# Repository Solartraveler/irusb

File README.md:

# IRUSB
This project is is a small board for sending infrared controller codes from a PC.
Receiving IR codes is possible too, but was not the main objective of this project.

## Host program

A host program for communicating is provided.
Written in python, it is platform independent - Linux and Windows were tested.

It all goes down to call the program like

./irusb-control.py 2 0xff00 0

Where the first parameter is the protocol, the second the address and the third the command.

You can add a TSOP31236 and call the host program without a parameter. Then press the key, you want to send later, on your existing infrared remote. The program then will print out the protocol, address and command discovered.

When installing the debian package, the same program can be called by the name irusb-control.

## Compiling and uploading

There is no additional programming hardware needed.

With apt install the packages gcc-arm-none-eabi, make, dfu-util and python3-usb.

Next, call make

Then close J4 and call ./dfu-upload.sh

Later, leave J4 open to directly start the flashed program.

## Debugging

You can add a serial port with 3.3V level to J3 and see some debug messages when using 19200baud.

Tested with a [NUCLEO-F411RE](https://www.st.com/en/evaluation-tools/nucleo-f411re.html), the software can be debugged. Open jumpers CN2 on the nucleo board and connect pins 2,3,4,5 of CN4 to the pins 2,3,4,5 of J2 on the IRUSB pcb.

## TODO

Create and publish a kicad symbol for a MCP1754-3302E_SOT23

## Libraries used and licenses

The software uses several open source libraries with different licenses.

The HAL library from ST is published under the BSD 3-Clause license.

Some CMSIS header files are published under the Apache 2.0 license.

The [IRMP](https://www.mikrocontroller.net/articles/IRMP_-_english) project is published under GPL 2.0 or later.

[Libusb_stm32](https://github.com/dmitrystu/libusb_stm32) is published under the Apache 2.0 license.

Since GPL 2.0 and Apache 2.0 are considered [incompatible](https://www.apache.org/licenses/GPL-compatibility.html) by the Free Software Foundation, but GPL 3.0 is considered compatible, GPL 3.0 is the only possible license for the firmware on the microcontroller side.

The PCB is under creative common license. [CC-BY-SA 3.0 DE](https://creativecommons.org/licenses/by-sa/3.0/de/deed.en)

## Windows users

Windows makes using USB devices a little bit more difficult. These steps are tested with Windows 10 64bit version 1903.

Install [python 3.9 for windows](https://www.python.org/downloads/windows/) and allow adding python to PATH.

Start cmd

Install pyusb with pip3 install pyusb

Now calling irusb-control.py will result in the error message "No backed available."

You will need a windows driver for IRUSB. [libusbK-inf-wizard.exe](https://sourceforge.net/projects/libusb-win32/files/libusb-win32-releases/libusbK-inf-wizard.exe) can generate one. I tried kernel driver package libusb0 v1.2.6.0. Select IRUSB (VID = 0x7700), then in the generated DriverPackages directory call InstallDriver.exe.

Now calling irusb-control.py should work.

## Alternate usage

The PCB can be used as simple testing board for other projects too. The project [stm32-verprog](https://github.com/dword1511/stm32-vserprog/) had already support for the same STM32 chip as used for IRUSB. So using a spare PCB as SPI flash chip programmer was easy.

Note: The socket shown on the picture is only 150mil in width, but flash chips typically require 200mil wide ones. So the flash chip is inserted upside down and the wires are mirrored accordingly.

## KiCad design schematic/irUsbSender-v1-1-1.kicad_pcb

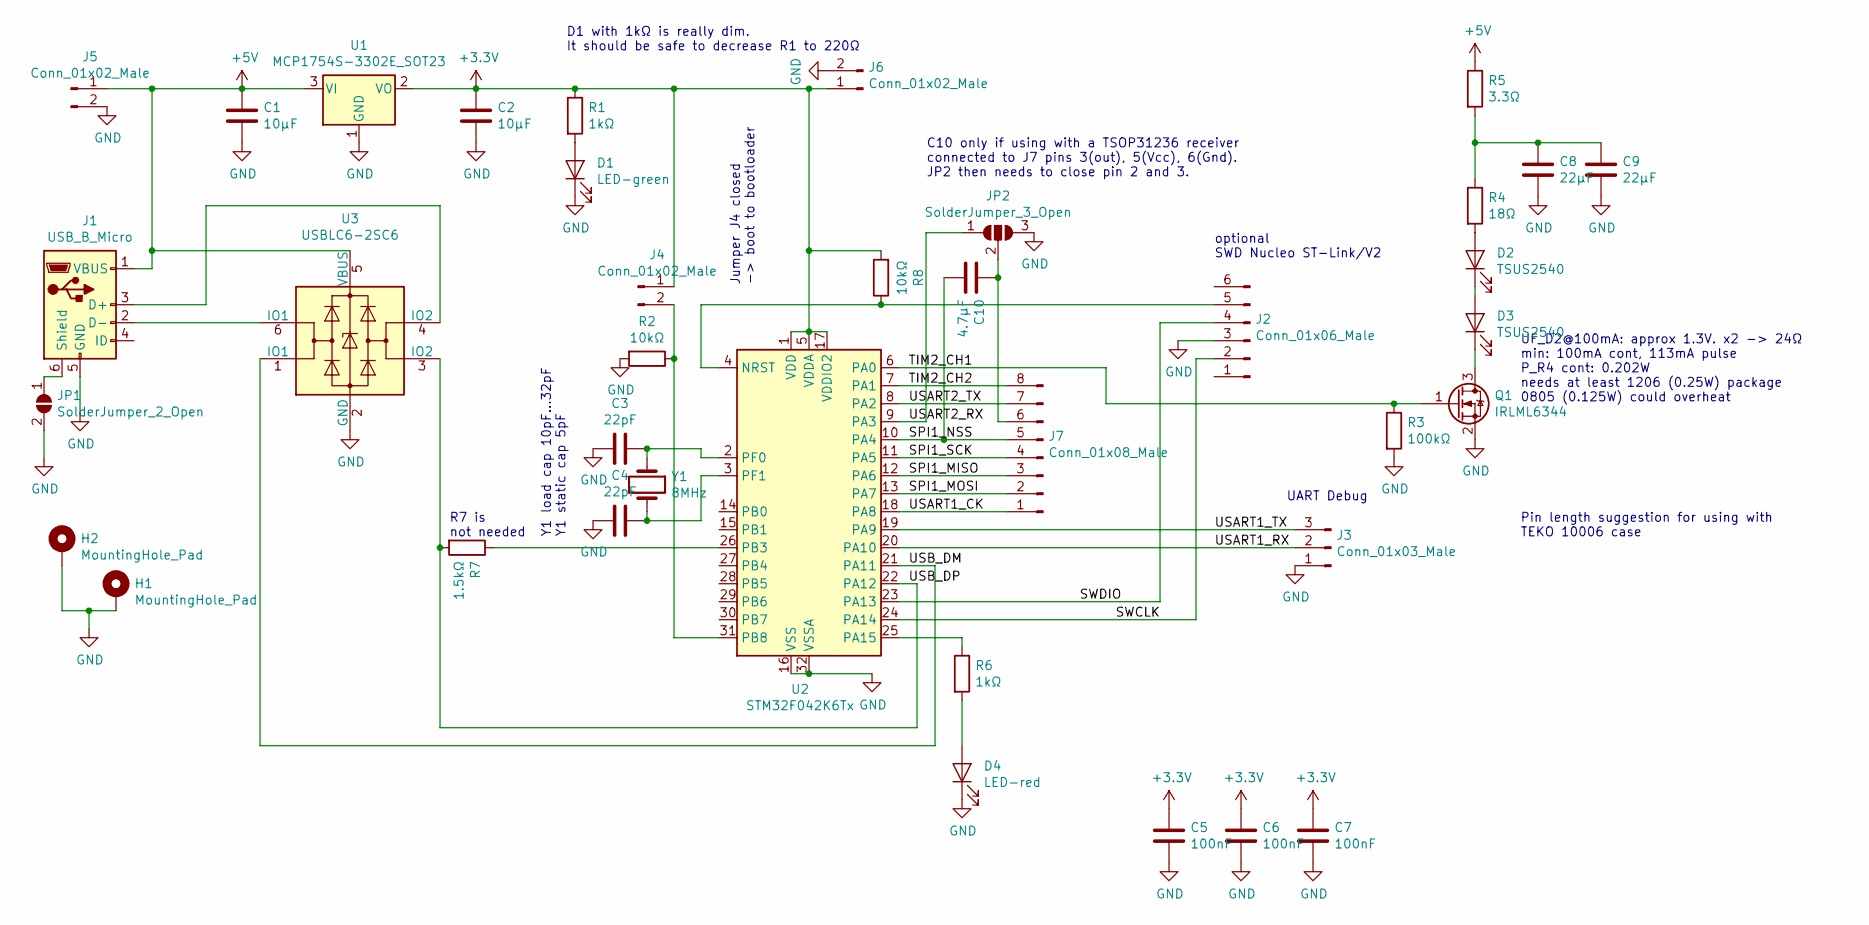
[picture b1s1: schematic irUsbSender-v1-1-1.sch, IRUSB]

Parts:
C1, C2: 10µF; C_0805_2012Metric_Pad1.15x1.40mm_HandSolder
C3, C4: 22pF; C_0805_2012Metric_Pad1.15x1.40mm_HandSolder
C5, C6, C7: 100nF; C_0805_2012Metric_Pad1.15x1.40mm_HandSolder
C8, C9: 22µF; C_1206_3216Metric_Pad1.42x1.75mm_HandSolder
C10: 4.7µF; C_0805_2012Metric_Pad1.15x1.40mm_HandSolder
D1: LED-green; LED_0805_2012Metric_Pad1.15x1.40mm_HandSolder
D2, D3: TSUS2540; LED_D5.0mm_IRGrey
D4: LED-red; LED_0805_2012Metric_Pad1.15x1.40mm_HandSolder
H1, H2: MountingHole_Pad; MountingHole_2.7mm_M2.5_Pad
J1: USB_B_Micro; USB_Micro-B_Amtek-MIUSB-F5M-BBX-U_Handsolder
J2: Conn_01x06_Male; PinHeader_1x06_P2.54mm_Vertical
J3: Conn_01x03_Male; PinSocket_1x03_P2.54mm_Vertical
J4: Conn_01x02_Male; PinHeader_1x02_P2.54mm_Vertical
J5, J6: Conn_01x02_Male; TestPoint_2Pads_Pitch2.54mm_Drill0.8mm
J7: Conn_01x08_Male; PinSocket_1x08_P2.54mm_Vertical
JP1: SolderJumper_2_Open; SolderJumper-2_P1.3mm_Open_Pad1.0x1.5mm
JP2: SolderJumper_3_Open; SolderJumper-3_P1.3mm_Open_Pad1.0x1.5mm
Q1: IRLML6344; SOT-23_Handsoldering
R1, R6: 1kΩ; R_0805_2012Metric_Pad1.15x1.40mm_HandSolder
R2, R8: 10kΩ; R_0805_2012Metric_Pad1.15x1.40mm_HandSolder
R3: 100kΩ; R_0805_2012Metric_Pad1.15x1.40mm_HandSolder
R4: 18Ω; R_1206_3216Metric_Pad1.42x1.75mm_HandSolder
R5: 3.3Ω; R_0805_2012Metric_Pad1.15x1.40mm_HandSolder
R7: 1.5kΩ; R_0805_2012Metric_Pad1.15x1.40mm_HandSolder
U1: MCP1754S-3302E_SOT23; SOT-23_Handsoldering
U2: STM32F042K6Tx; LQFP-32_7x7mm_P0.8mm
U3: USBLC6-2SC6; SOT-23-6_Handsoldering
Y1: 8MHz; Crystal_HC49-U_Vertical

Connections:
+3V3: C2.1, C5.2, C6.2, C7.2, J4.1, J6.1, R1.1, R8.2, U1.2 (VO), U2.1 (VDD), U2.5 (VDDA), U2.17 (VDDIO2)
+5V: C1.1, J1.1 (VBUS), J5.1, R5.1, U1.3 (VI), U3.5 (VBUS)
/SPI1_MISO: J7.3, U2.12 (PA6)
/SPI1_MOSI: J7.2, U2.13 (PA7)
/SPI1_NSS: C10.1, J7.5, U2.10 (PA4)
/SPI1_SCK: J7.4, U2.11 (PA5)
/SWCLK: J2.2, U2.24 (PA14)
/SWDIO: J2.4, U2.23 (PA13)
/TIM2_CH1: Q1.1 (G), R3.1, U2.6 (PA0)
/TIM2_CH2: J7.8, U2.7 (PA1)
/USART1_CK: J7.1, U2.18 (PA8)
/USART1_RX: J3.2, U2.20 (PA10)
/USART1_TX: J3.3, U2.19 (PA9)
/USART2_RX: JP2.1 (A), U2.9 (PA3)
/USART2_TX: J7.7, U2.8 (PA2)
/USB_DM: U2.21 (PA11), U3.1 (IO1)
/USB_DP: R7.2, U2.22 (PA12), U3.3 (IO2)
GND: C1.2, C2.2, C3.2, C4.2, C5.1, C6.1, C7.1, C8.2, C9.2, D1.1 (K), D4.1 (K), H1.1, H2.1, J1.5 (GND), J2.3, J3.1, J5.2, J6.2, JP1.2 (B), JP2.3 (B), Q1.2 (S), R2.2, R3.2, U1.1 (GND), U2.16 (VSS), U2.32 (VSSA), U3.2 (GND)
unnamed: C3.1, U2.2 (PF0), Y1.1
unnamed: C4.1, U2.3 (PF1), Y1.2
unnamed: C8.1, C9.1, R4.1, R5.2
unnamed: C10.2, J7.6, JP2.2 (C)
unnamed: D1.2 (A), R1.2
unnamed: D2.1 (K), D3.2 (A)
unnamed: D2.2 (A), R4.2
unnamed: D3.1 (K), Q1.3 (D)
unnamed: D4.2 (A), R6.2
unnamed: J1.2 (D-), U3.6 (IO1)
unnamed: J1.3 (D+), U3.4 (IO2)
unnamed: J1.6 (Shield), JP1.1 (A)
unnamed: J2.5, R8.1, U2.4 (NRST)
unnamed: J4.2, R2.1, U2.31 (PB8)
unnamed: R6.1, U2.25 (PA15)
unnamed: R7.1, U2.26 (PB3)

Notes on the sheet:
optional SWD Nucleo ST-Link/V2
Jumper J4 closed -> boot to bootloader
UART Debug
UF_D2@100mA: approx 1.3V. x2 -> 24Ω min: 100mA cont, 113mA pulse P_R4 cont: 0.202W needs at least 1206 (0.25W) package 0805 (0.125W) could overheat
Y1 load cap 10pF...32pF Y1 static cap 5pF
C10 only if using with a TSOP31236 receiver connected to J7 pins 3(out), 5(Vcc), 6(Gnd). JP2 then needs to close pin 2 and 3.
R7 is not needed
D1 with 1kΩ is really dim. It should be safe to decrease R1 to 220Ω
Pin length suggestion for using with TEKO 10006 case

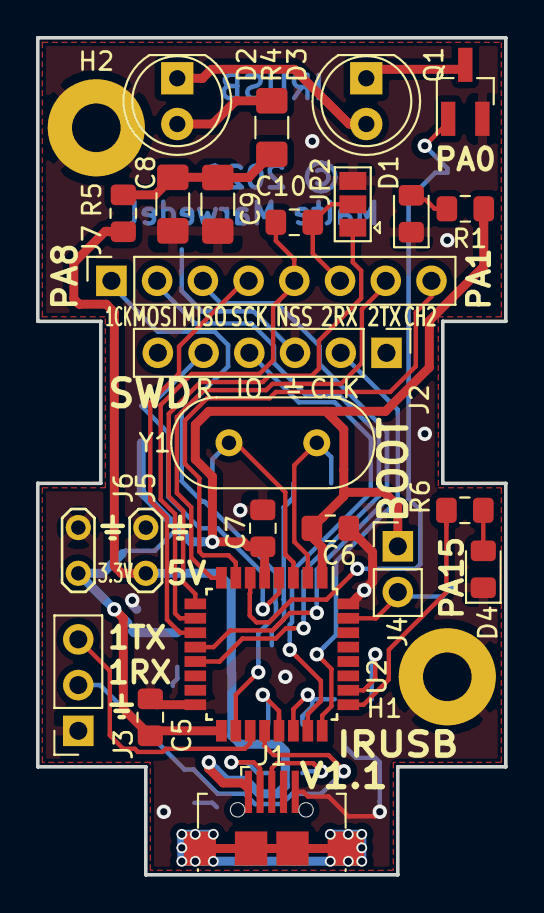
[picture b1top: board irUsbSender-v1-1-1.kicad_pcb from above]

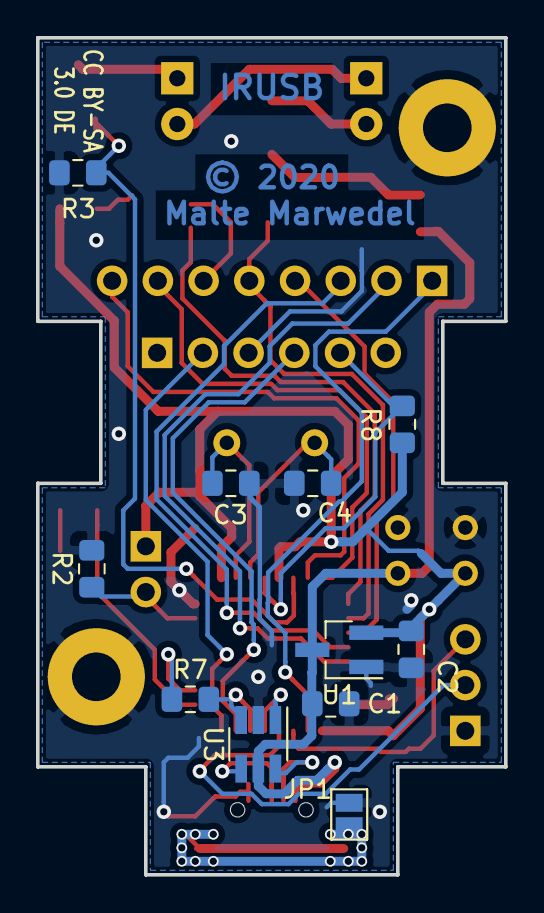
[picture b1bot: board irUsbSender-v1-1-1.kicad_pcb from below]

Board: 2 copper layers, 26.0 x 46.5 mm, 38 parts (11 on the bottom side), 34 nets.

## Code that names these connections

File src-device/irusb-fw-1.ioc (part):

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PA2.GPIO_PuPd=GPIO_PULLDOWN
Mcu.UserName=STM32F042K6Tx
PA10.GPIO_PuPd=GPIO_PULLUP
PA3.GPIO_PuPd=GPIO_PULLDOWN
PA11.Mode=Device
PA3.GPIOParameters=GPIO_PuPd
PA6.GPIO_Label=IrRxIn
PA2.GPIOParameters=GPIO_PuPd
RCC.SYSCLKSource=RCC_SYSCLKSOURCE_PLLCLK
PB5.GPIOParameters=GPIO_PuPd
PA15.GPIO_Label=LedRed
PB4.GPIOParameters=GPIO_PuPd
PA12.Signal=USB_DP
PB1.GPIO_PuPd=GPIO_PULLDOWN
PB6.Signal=GPIO_Input
PA8.GPIOParameters=GPIO_PuPd
PA1.GPIO_PuPd=GPIO_PULLDOWN
PB0.GPIOParameters=GPIO_PuPd
PA13.GPIO_PuPd=GPIO_PULLDOWN
PA6.GPIO_PuPd=GPIO_PULLUP
PB3.GPIO_PuPd=GPIO_PULLDOWN
PA1.GPIOParameters=GPIO_PuPd
PA5.GPIO_PuPd=GPIO_PULLDOWN
PB3.GPIOParameters=GPIO_PuPd,GPIO_Label
PB7.Signal=GPIO_Input
PA8.Signal=GPIO_Input
PB6.GPIOParameters=GPIO_PuPd
PA0.Signal=S_TIM2_CH1_ETR
PA13.GPIOParameters=GPIO_PuPd
Mcu.Package=LQFP32
PB1.Signal=GPIO_Input
PA6.Signal=GPIO_Input
PA10.Signal=USART1_RX
PA15.Signal=GPIO_Output
PA5.GPIOParameters=GPIO_PuPd
PF1-OSC_OUT.Mode=HSE-External-Oscillator
PA4.GPIO_Label=IrRxPower
PF1-OSC_OUT.Signal=RCC_OSC_OUT
PB4.Signal=GPIO_Input
PA3.Signal=GPIO_Input
PB3.GPIO_Label=UsbReset
PA6.GPIOParameters=GPIO_PuPd,GPIO_Label
PB7.GPIO_PuPd=GPIO_PULLDOWN
PB8.GPIOParameters=GPIO_Label
PA10.Mode=Asynchronous
PA15.GPIOParameters=GPIO_Label
PB6.GPIO_PuPd=GPIO_PULLDOWN
PA13.Signal=GPIO_Input
PB8.GPIO_Label=BootInput
PA9.Mode=Asynchronous
PA4.PinState=GPIO_PIN_SET
PB7.GPIOParameters=GPIO_PuPd
PA9.Signal=USART1_TX
PB4.GPIO_PuPd=GPIO_PULLDOWN
PA7.GPIO_PuPd=GPIO_PULLDOWN
PA1.Signal=GPIO_Input
PF0-OSC_IN.Mode=HSE-External-Oscillator
PA5.Signal=GPIO_Input
board=custom
PA10.GPIOParameters=GPIO_PuPd
PA4.GPIOParameters=PinState,GPIO_Label
PA14.GPIO_PuPd=GPIO_PULLDOWN
Mcu.Name=STM32F042K(4-6)Tx
PA2.Signal=GPIO_Input
PB3.Signal=GPIO_Input
PA4.Signal=GPIO_Output
RCC.SYSCLKFreq_VALUE=48000000
PB5.Signal=GPIO_Input
PA12.Mode=Device
PA14.GPIOParameters=GPIO_PuPd
PB5.GPIO_PuPd=GPIO_PULLDOWN
PA11.Signal=USB_DM
PA14.Signal=GPIO_Input
PA8.GPIO_PuPd=GPIO_PULLDOWN
PB8.Signal=GPIO_Input
PF0-OSC_IN.Signal=RCC_OSC_IN
PB0.Signal=GPIO_Input
PA7.GPIOParameters=GPIO_PuPd
PB0.GPIO_PuPd=GPIO_PULLDOWN
PB1.GPIOParameters=GPIO_PuPd
PA7.Signal=GPIO_Input

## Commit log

2020-11-27 Initial checkin version 0.9
2020-11-28 Add build workflow. Add cnc milling. Improve doc. Minor fix in schematic. Minor improvement in host program.
2020-12-09 Change USB PID to granted type. Fix iwdg timeout. Add udev rule
2020-12-12 Rename irusbControl to irusb-control. Add files for debian package generation. Add howto for Windows users.
2020-12-12 Fixing makefile paths
2020-12-12 Try to get the runner working
2020-12-12 Add forgotten files for package generation
2021-10-13 Add fixed schematic and board - version 1.1.1. Add description about alternate usage as flash chip programmer
2021-10-13 Add kicad cache file to have the symbols not part of the official lib, or should the official lib change.
2021-12-05 Typo fixed

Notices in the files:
schematic/irUsbSender-v1-1-1.kicad_pcb:
(c) 2020 by Malte Marwedel
© 2020
